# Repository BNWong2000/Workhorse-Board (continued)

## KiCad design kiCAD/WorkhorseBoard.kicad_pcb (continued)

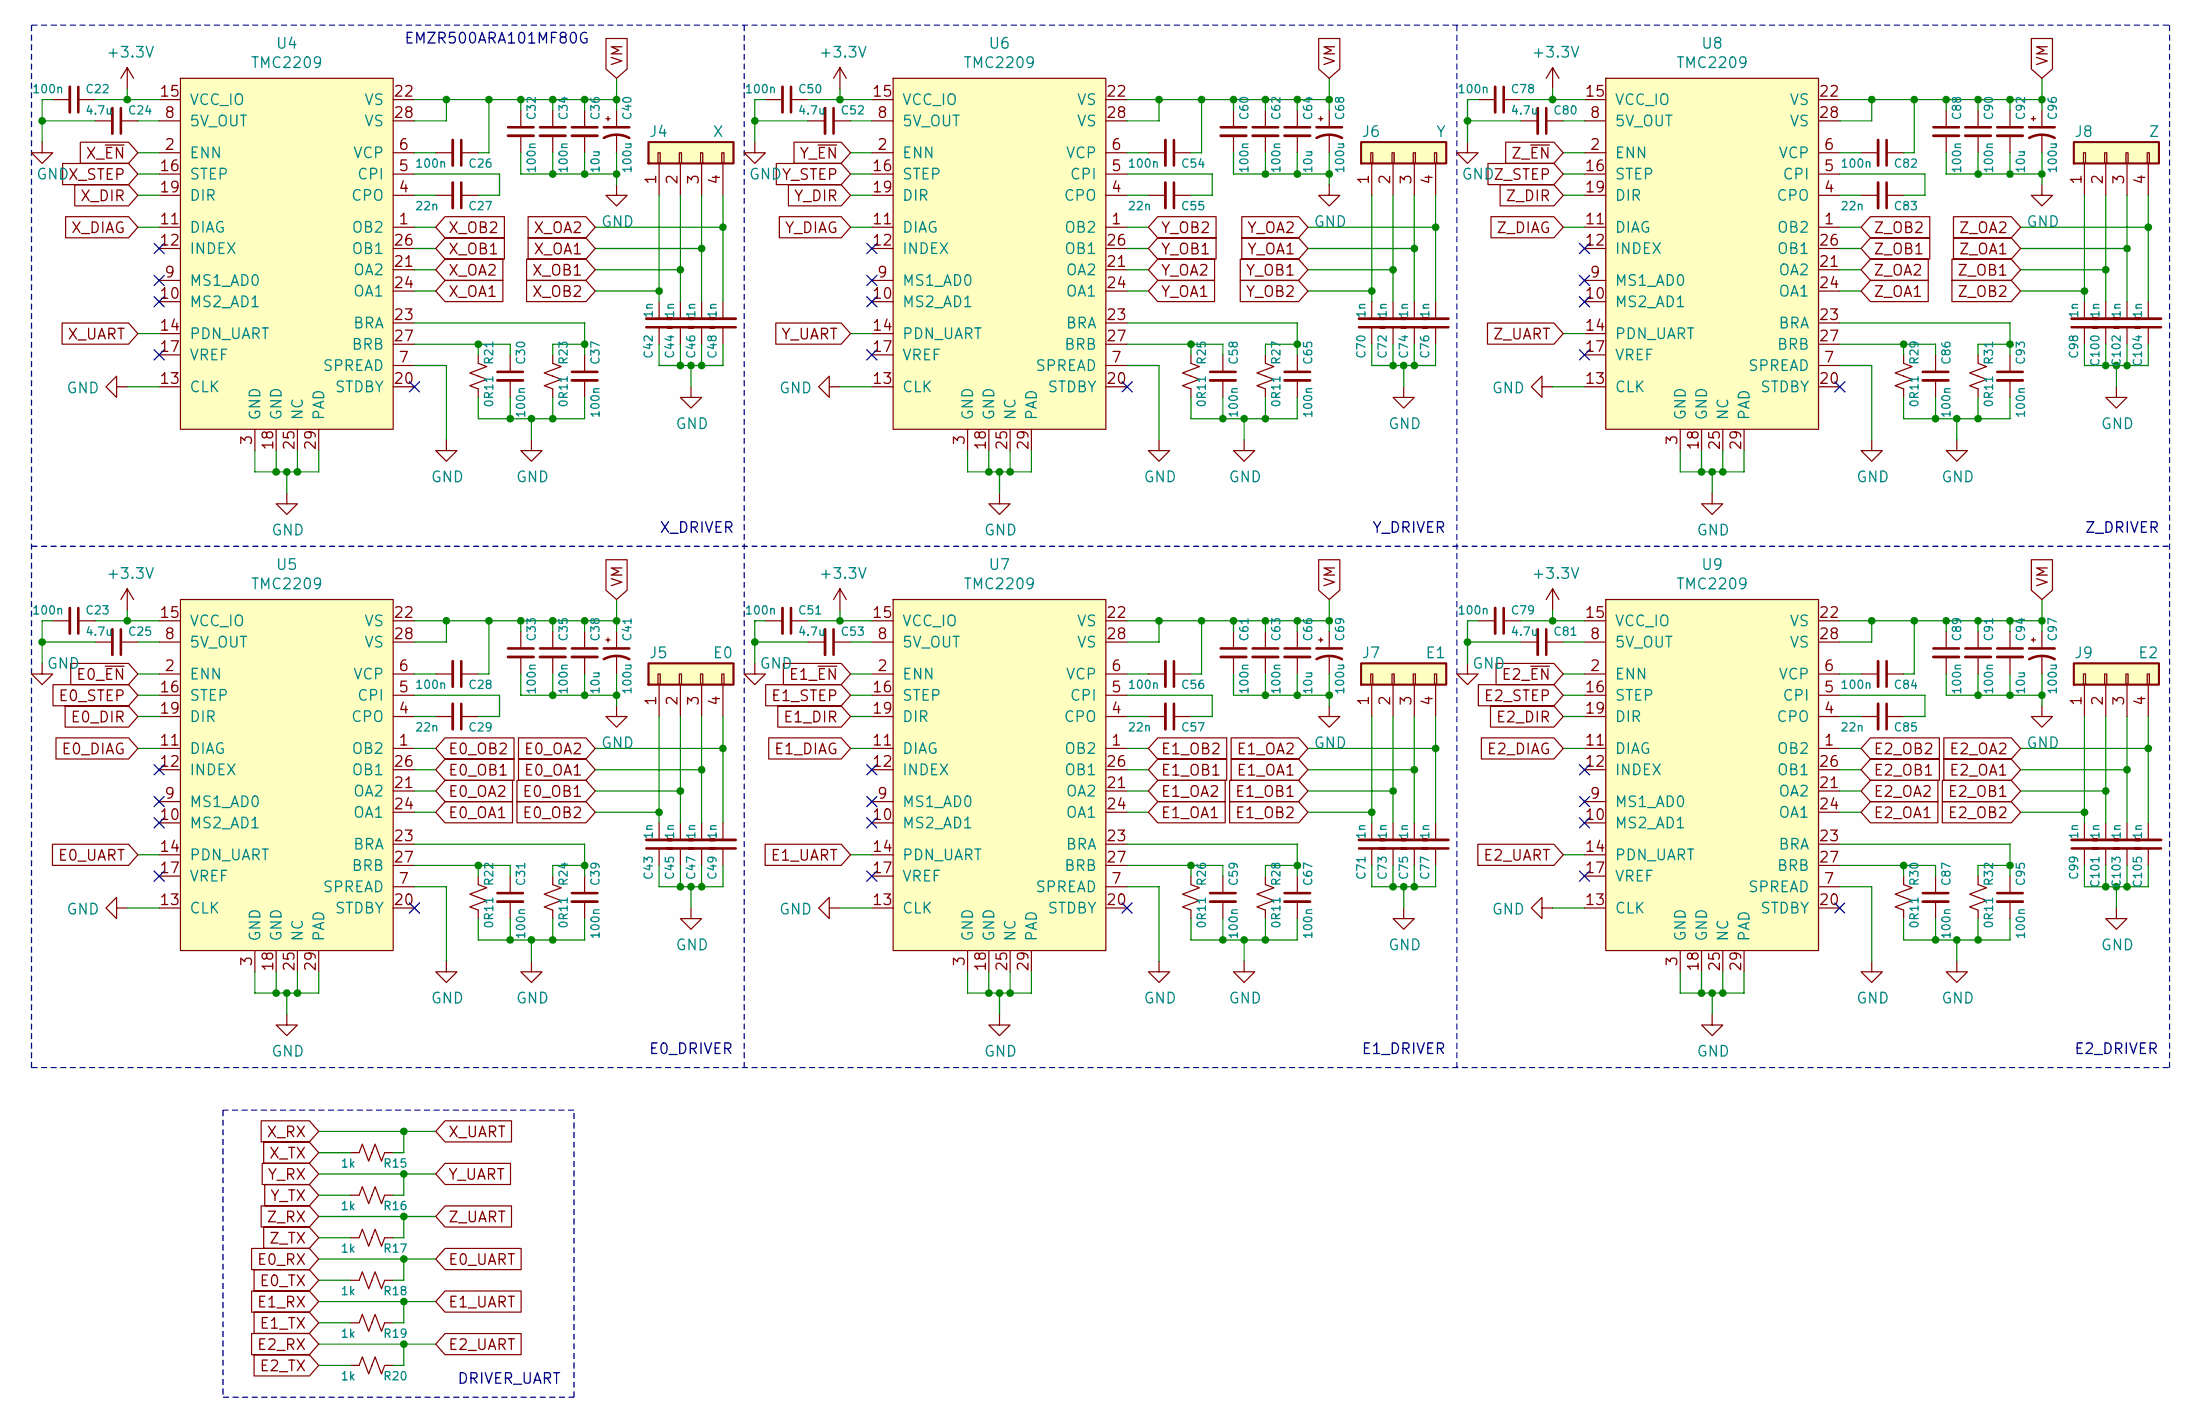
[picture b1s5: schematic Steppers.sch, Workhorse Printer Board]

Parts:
C22, C23, C26, C28, C30, C31, C32, C33, C34, C35, C37, C39, C50, C51, C54, C56, C58, C59, C60, C61, C62, C63, C65, C67, C78, C79, C82, C84, C86, C87, C88, C89, C90, C91, C93, C95: 100n; C_0603_1608Metric_Pad1.05x0.95mm_HandSolder
C24, C25, C52, C53, C80, C81: 4.7u; C_0603_1608Metric_Pad1.05x0.95mm_HandSolder
C27, C29, C55, C57, C83, C85: 22n; C_0603_1608Metric_Pad1.05x0.95mm_HandSolder
C36, C38, C64, C66, C92, C94: 10u; C_1206_3216Metric_Pad1.42x1.75mm_HandSolder
C40, C41, C68, C69, C96, C97: 100u; CP_Elec_6.3x7.7
C42, C43, C44, C45, C46, C47, C48, C49, C70, C71, C72, C73, C74, C75, C76, C77, C98, C99, C100, C101, C102, C103, C104, C105: 1n; C_0603_1608Metric_Pad1.05x0.95mm_HandSolder
J4: X; Molex_KK-254_AE-6410-04A_1x04_P2.54mm_Vertical
J5: E0; Molex_KK-254_AE-6410-04A_1x04_P2.54mm_Vertical
J6: Y; Molex_KK-254_AE-6410-04A_1x04_P2.54mm_Vertical
J7: E1; Molex_KK-254_AE-6410-04A_1x04_P2.54mm_Vertical
J8: Z; Molex_KK-254_AE-6410-04A_1x04_P2.54mm_Vertical
J9: E2; Molex_KK-254_AE-6410-04A_1x04_P2.54mm_Vertical
R15, R16, R17, R18, R19, R20: 1k; R_0603_1608Metric_Pad1.05x0.95mm_HandSolder
R21, R22, R23, R24, R25, R26, R27, R28, R29, R30, R31, R32: 0R11; R_0805_2012Metric_Pad1.15x1.40mm_HandSolder
U4, U5, U6, U7, U8, U9: TMC2209; QFN-28-1EP_5x5mm_P0.5mm_EP3.35x3.35mm_ThermalVias

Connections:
+3V3: C22.1, C23.1, C50.1, C51.1, C78.1, C79.1, U4.15 (VCC_IO), U5.15 (VCC_IO), U6.15 (VCC_IO), U7.15 (VCC_IO), U8.15 (VCC_IO), U9.15 (VCC_IO); also elsewhere on the board
E0_DIAG: U5.11 (DIAG); also elsewhere on the board
E0_DIR: U5.19 (DIR); also elsewhere on the board
E0_OA1: C47.2, J5.3, U5.24 (OA1)
E0_OA2: C49.2, J5.4, U5.21 (OA2)
E0_OB1: C45.2, J5.2, U5.26 (OB1)
E0_OB2: C43.2, J5.1, U5.1 (OB2)
E0_RX: R18.1, U5.14 (PDN_UART); also elsewhere on the board
E0_STEP: U5.16 (STEP); also elsewhere on the board
E0_TX: R18.2; also elsewhere on the board
E0_~EN: U5.2 (ENN); also elsewhere on the board
E1_DIAG: U7.11 (DIAG); also elsewhere on the board
E1_DIR: U7.19 (DIR); also elsewhere on the board
E1_OA1: C75.2, J7.3, U7.24 (OA1)
E1_OA2: C77.2, J7.4, U7.21 (OA2)
E1_OB1: C73.2, J7.2, U7.26 (OB1)
E1_OB2: C71.2, J7.1, U7.1 (OB2)
E1_RX: R19.1, U7.14 (PDN_UART); also elsewhere on the board
E1_STEP: U7.16 (STEP); also elsewhere on the board
E1_TX: R19.2; also elsewhere on the board
E1_~EN: U7.2 (ENN); also elsewhere on the board
E2_DIAG: U9.11 (DIAG); also elsewhere on the board
E2_DIR: U9.19 (DIR); also elsewhere on the board
E2_OA1: C103.2, J9.3, U9.24 (OA1)
E2_OA2: C105.2, J9.4, U9.21 (OA2)
E2_OB1: C101.2, J9.2, U9.26 (OB1)
E2_OB2: C99.2, J9.1, U9.1 (OB2)
E2_RX: R20.1, U9.14 (PDN_UART); also elsewhere on the board
E2_STEP: U9.16 (STEP); also elsewhere on the board
E2_TX: R20.2; also elsewhere on the board
E2_~EN: U9.2 (ENN); also elsewhere on the board
GND: C22.2, C23.2, C24.2, C25.2, C30.2, C31.2, C32.2, C33.2, C34.2, C35.2, C36.2, C37.2, C38.2, C39.2, C40.2, C41.2, C42.1, C43.1, C44.1, C45.1, C46.1, C47.1, C48.1, C49.1, C50.2, C51.2, C52.2, C53.2, C58.2, C59.2, C60.2, C61.2, C62.2, C63.2, C64.2, C65.2, C66.2, C67.2, C68.2, C69.2, C70.1, C71.1, C72.1, C73.1, C74.1, C75.1, C76.1, C77.1, C78.2, C79.2, C80.2, C81.2, C86.2, C87.2, C88.2, C89.2, C90.2, C91.2, C92.2, C93.2, C94.2, C95.2, C96.2, C97.2, C98.1, C99.1, C100.1, C101.1, C102.1, C103.1, C104.1, C105.1, R21.2, R22.2, R23.2, R24.2, R25.2, R26.2, R27.2, R28.2, R29.2, R30.2, R31.2, R32.2, U4.3 (GND), U4.7 (SPREAD), U4.13 (CLK), U4.18 (GND), U4.25 (NC), U4.29 (PAD), U5.3 (GND), U5.7 (SPREAD), U5.13 (CLK), U5.18 (GND), U5.25 (NC), U5.29 (PAD), U6.3 (GND), U6.7 (SPREAD), U6.13 (CLK), U6.18 (GND), U6.25 (NC), U6.29 (PAD), U7.3 (GND), U7.7 (SPREAD), U7.13 (CLK), U7.18 (GND), U7.25 (NC), U7.29 (PAD), U8.3 (GND), U8.7 (SPREAD), U8.13 (CLK), U8.18 (GND), U8.25 (NC), U8.29 (PAD), U9.3 (GND), U9.7 (SPREAD), U9.13 (CLK), U9.18 (GND), U9.25 (NC), U9.29 (PAD); also elsewhere on the board
unnamed: C24.1, U4.8 (5V_OUT)
unnamed: C25.1, U5.8 (5V_OUT)
unnamed: C26.2, U4.6 (VCP)
unnamed: C27.1, U4.5 (CPI)
unnamed: C27.2, U4.4 (CPO)
unnamed: C28.2, U5.6 (VCP)
unnamed: C29.1, U5.5 (CPI)
unnamed: C29.2, U5.4 (CPO)
unnamed: C30.1, R21.1, U4.27 (BRB)
unnamed: C31.1, R22.1, U5.27 (BRB)
unnamed: C37.1, R23.1, U4.23 (BRA)
unnamed: C39.1, R24.1, U5.23 (BRA)
unnamed: C52.1, U6.8 (5V_OUT)
unnamed: C53.1, U7.8 (5V_OUT)
unnamed: C54.2, U6.6 (VCP)
unnamed: C55.1, U6.5 (CPI)
unnamed: C55.2, U6.4 (CPO)
unnamed: C56.2, U7.6 (VCP)
unnamed: C57.1, U7.5 (CPI)
unnamed: C57.2, U7.4 (CPO)
unnamed: C58.1, R25.1, U6.27 (BRB)
unnamed: C59.1, R26.1, U7.27 (BRB)
unnamed: C65.1, R27.1, U6.23 (BRA)
unnamed: C67.1, R28.1, U7.23 (BRA)
unnamed: C80.1, U8.8 (5V_OUT)
unnamed: C81.1, U9.8 (5V_OUT)
unnamed: C82.2, U8.6 (VCP)
unnamed: C83.1, U8.5 (CPI)
unnamed: C83.2, U8.4 (CPO)
unnamed: C84.2, U9.6 (VCP)
unnamed: C85.1, U9.5 (CPI)
unnamed: C85.2, U9.4 (CPO)
unnamed: C86.1, R29.1, U8.27 (BRB)
unnamed: C87.1, R30.1, U9.27 (BRB)
unnamed: C93.1, R31.1, U8.23 (BRA)
unnamed: C95.1, R32.1, U9.23 (BRA)
VM: C26.1, C28.1, C32.1, C33.1, C34.1, C35.1, C36.1, C38.1, C40.1, C41.1, C54.1, C56.1, C60.1, C61.1, C62.1, C63.1, C64.1, C66.1, C68.1, C69.1, C82.1, C84.1, C88.1, C89.1, C90.1, C91.1, C92.1, C94.1, C96.1, C97.1, U4.22 (VS), U4.28 (VS), U5.22 (VS), U5.28 (VS), U6.22 (VS), U6.28 (VS), U7.22 (VS), U7.28 (VS), U8.22 (VS), U8.28 (VS), U9.22 (VS), U9.28 (VS); also elsewhere on the board
X_DIAG: U4.11 (DIAG); also elsewhere on the board
X_DIR: U4.19 (DIR); also elsewhere on the board
X_OA1: C46.2, J4.3, U4.24 (OA1)
X_OA2: C48.2, J4.4, U4.21 (OA2)
X_OB1: C44.2, J4.2, U4.26 (OB1)
X_OB2: C42.2, J4.1, U4.1 (OB2)
X_RX: R15.1, U4.14 (PDN_UART); also elsewhere on the board
X_STEP: U4.16 (STEP); also elsewhere on the board
X_TX: R15.2; also elsewhere on the board
X_~EN: U4.2 (ENN); also elsewhere on the board
Y_DIAG: U6.11 (DIAG); also elsewhere on the board
Y_DIR: U6.19 (DIR); also elsewhere on the board
Y_OA1: C74.2, J6.3, U6.24 (OA1)
Y_OA2: C76.2, J6.4, U6.21 (OA2)
Y_OB1: C72.2, J6.2, U6.26 (OB1)
Y_OB2: C70.2, J6.1, U6.1 (OB2)
Y_RX: R16.1, U6.14 (PDN_UART); also elsewhere on the board
Y_STEP: U6.16 (STEP); also elsewhere on the board
Y_TX: R16.2; also elsewhere on the board
Y_~EN: U6.2 (ENN); also elsewhere on the board
Z_DIAG: U8.11 (DIAG); also elsewhere on the board
Z_DIR: U8.19 (DIR); also elsewhere on the board
Z_OA1: C102.2, J8.3, U8.24 (OA1)
Z_OA2: C104.2, J8.4, U8.21 (OA2)
Z_OB1: C100.2, J8.2, U8.26 (OB1)
Z_OB2: C98.2, J8.1, U8.1 (OB2)
Z_RX: R17.1, U8.14 (PDN_UART); also elsewhere on the board
Z_STEP: U8.16 (STEP); also elsewhere on the board
Z_TX: R17.2; also elsewhere on the board
Z_~EN: U8.2 (ENN); also elsewhere on the board

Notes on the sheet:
DRIVER_UART
X_DRIVER
Y_DRIVER
Z_DRIVER
E0_DRIVER
E1_DRIVER
E2_DRIVER
EMZR500ARA101MF80G

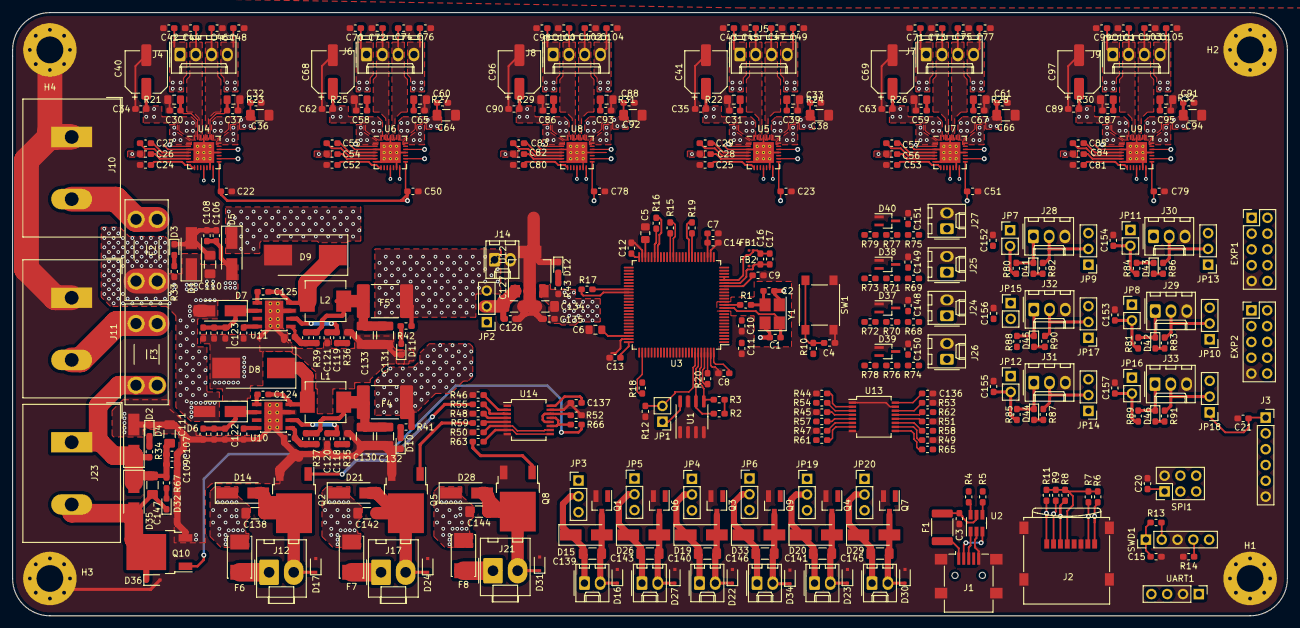
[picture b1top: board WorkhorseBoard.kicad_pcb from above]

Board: 4 copper layers, 205.0 x 97.0 mm, 385 parts (0 on the bottom side), 259 nets.

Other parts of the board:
C148, C149, C150, C151: 100n; C_0603_1608Metric_Pad1.05x0.95mm_HandSolder
D37, D38, D39, D40: BAV99W; SOT-323_SC-70_Handsoldering
J24, J25, J26, J27: Conn_01x02; Molex_KK-254_AE-6410-02A_1x02_P2.54mm_Vertical
R68, R69, R70, R71, R74, R75, R76, R77: 2.37k; R_0603_1608Metric_Pad1.05x0.95mm_HandSolder
R72, R73, R78, R79: 4.7k; R_0603_1608Metric_Pad1.05x0.95mm_HandSolder

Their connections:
+3V3: D37.2, D38.2, D39.2, D40.2, R72.1, R73.1, R78.1, R79.1; also elsewhere on the board
GND: C148.2, C149.2, C150.2, C151.2, D37.1, D38.1, D39.1, D40.1, J24.2, J25.2, J26.2, J27.2; also elsewhere on the board
unnamed: D37.3, R68.1, R70.2
unnamed: D38.3, R69.1, R71.2
unnamed: D39.3, R74.1, R76.2
unnamed: D40.3, R75.1, R77.2
unnamed: J24.1, R70.1, R72.2
unnamed: J25.1, R71.1, R73.2
unnamed: J26.1, R76.1, R78.2
unnamed: J27.1, R77.1, R79.2
T0: C148.1, R68.2; also elsewhere on the board
T1: C150.1, R74.2; also elsewhere on the board
T2: C149.1, R69.2; also elsewhere on the board
TB: C151.1, R75.2; also elsewhere on the board

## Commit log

2020-11-13 Completed Schematic, assigned footprints.
2020-11-14 started layout
2020-11-14 small fix
2020-11-14 started laying out drivers
2020-11-15 layed out TMC's and started laying out power electronics
2020-11-23 fixed placement slightly to improve cooling
2020-11-24 did layout for FETs and redid layout for Power input
2020-11-25 finished layout of everything but endstops.
2020-11-25 Started tracing
2020-11-25 small changes.
2020-11-27 added power plane
2020-11-30 Re-did fills
2020-11-30 refined some of the fills, started routing.
2020-12-07 slight change to TMC layout.
